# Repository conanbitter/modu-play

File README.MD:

# ModuPlay

*The console that's only as smart as the cartridge you plug in.*

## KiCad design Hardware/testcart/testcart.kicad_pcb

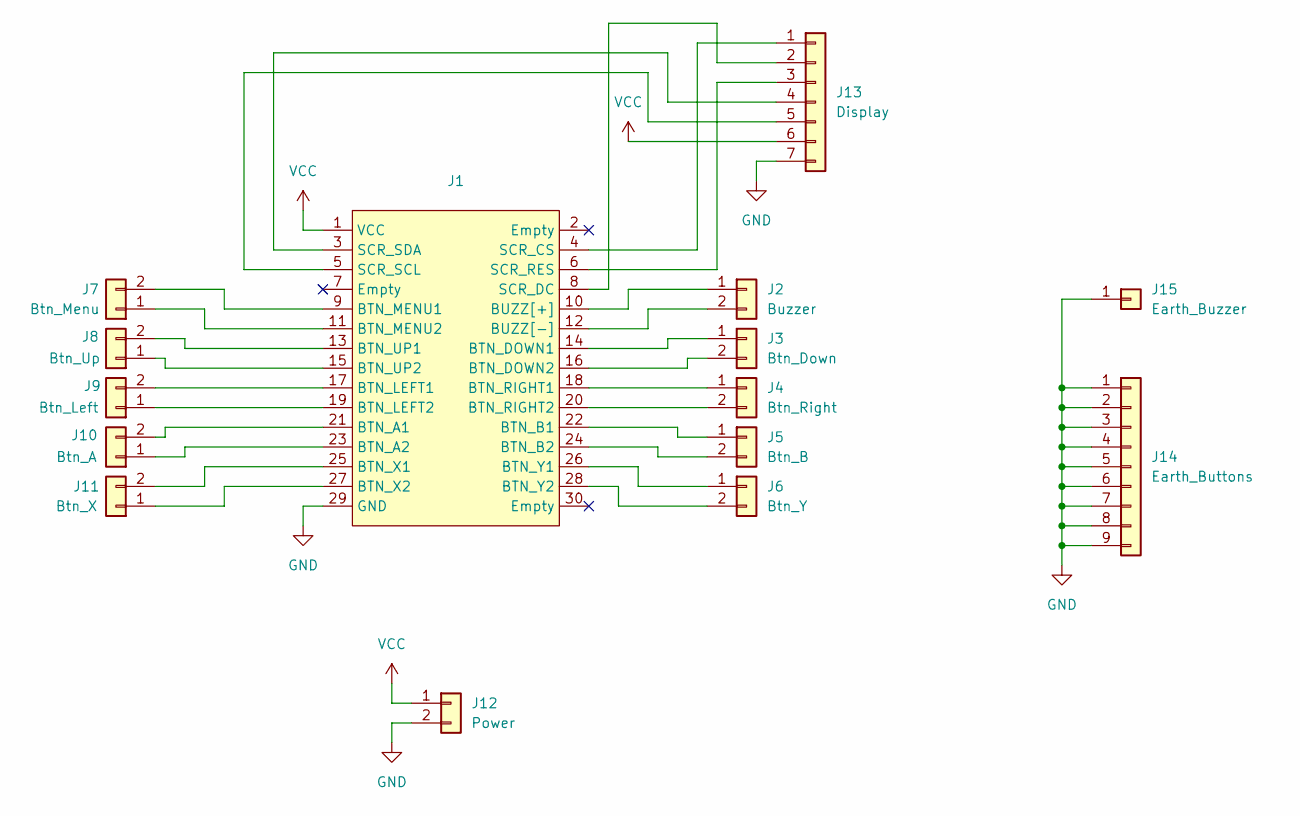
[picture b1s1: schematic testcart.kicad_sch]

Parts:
J1: Edge_Connector
J2: Buzzer; PinHeader_1x02_P2.54mm_Vertical
J3: Btn_Down; PinHeader_1x02_P2.54mm_Vertical
J4: Btn_Right; PinHeader_1x02_P2.54mm_Vertical
J5: Btn_B; PinHeader_1x02_P2.54mm_Vertical
J6: Btn_Y; PinHeader_1x02_P2.54mm_Vertical
J7: Btn_Menu; PinHeader_1x02_P2.54mm_Vertical
J8: Btn_Up; PinHeader_1x02_P2.54mm_Vertical
J9: Btn_Left; PinHeader_1x02_P2.54mm_Vertical
J10: Btn_A; PinHeader_1x02_P2.54mm_Vertical
J11: Btn_X; PinHeader_1x02_P2.54mm_Vertical
J12: Power; PinHeader_1x02_P2.54mm_Vertical
J13: Display; PinHeader_1x07_P2.54mm_Vertical
J14: Earth_Buttons; PinHeader_1x09_P2.54mm_Vertical
J15: Earth_Buzzer; PinHeader_1x01_P2.54mm_Vertical

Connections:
GND: J1.29 (GND), J12.2, J13.7, J14.1, J14.2, J14.3, J14.4, J14.5, J14.6, J14.7, J14.8, J14.9, J15.1
unnamed: J1.21 (BTN_A1), J10.2
unnamed: J1.23 (BTN_A2), J10.1
unnamed: J1.22 (BTN_B1), J5.1
unnamed: J1.24 (BTN_B2), J5.2
unnamed: J1.14 (BTN_DOWN1), J3.1
unnamed: J1.16 (BTN_DOWN2), J3.2
unnamed: J1.17 (BTN_LEFT1), J9.2
unnamed: J1.19 (BTN_LEFT2), J9.1
unnamed: J1.9 (BTN_MENU1), J7.2
unnamed: J1.11 (BTN_MENU2), J7.1
unnamed: J1.18 (BTN_RIGHT1), J4.1
unnamed: J1.20 (BTN_RIGHT2), J4.2
unnamed: J1.13 (BTN_UP1), J8.2
unnamed: J1.15 (BTN_UP2), J8.1
unnamed: J1.25 (BTN_X1), J11.2
unnamed: J1.27 (BTN_X2), J11.1
unnamed: J1.26 (BTN_Y1), J6.1
unnamed: J1.28 (BTN_Y2), J6.2
unnamed: J1.10 (BUZZ[+]), J2.1
unnamed: J1.12 (BUZZ[-]), J2.2
unnamed: J1.4 (SCR_CS), J13.1
unnamed: J1.8 (SCR_DC), J13.2
unnamed: J1.6 (SCR_RES), J13.3
unnamed: J1.5 (SCR_SCL), J13.5
unnamed: J1.3 (SCR_SDA), J13.4
VCC: J1.1 (VCC), J12.1, J13.6

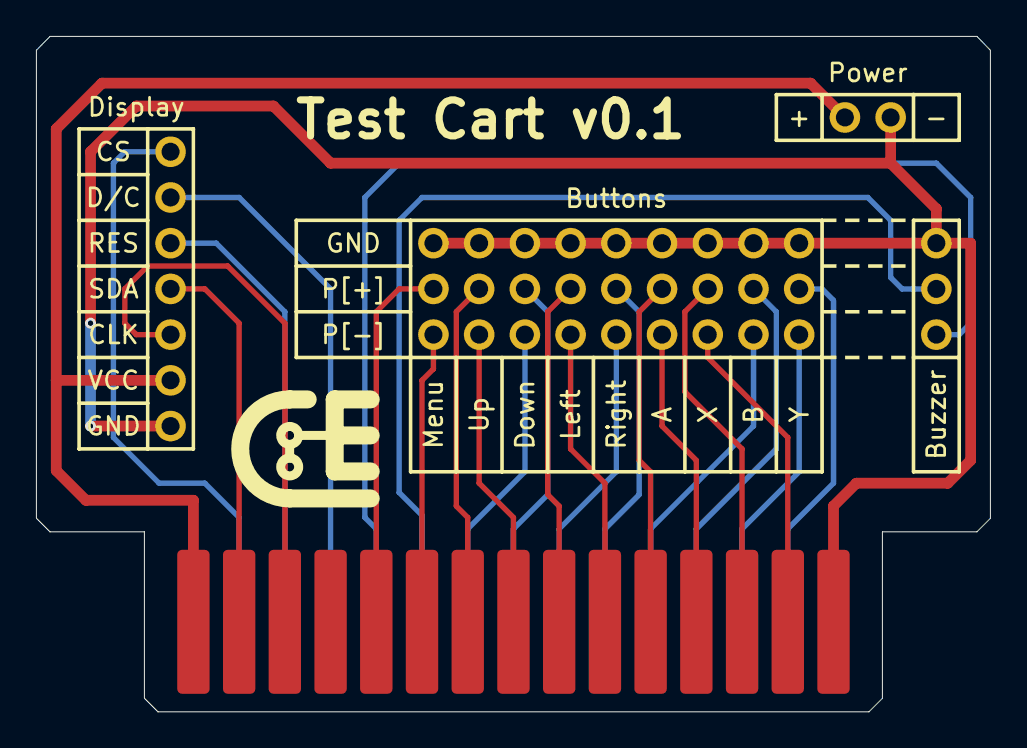
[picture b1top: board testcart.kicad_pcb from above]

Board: 2 copper layers, 53.0 x 37.5 mm, 15 parts (0 on the bottom side), 27 nets.

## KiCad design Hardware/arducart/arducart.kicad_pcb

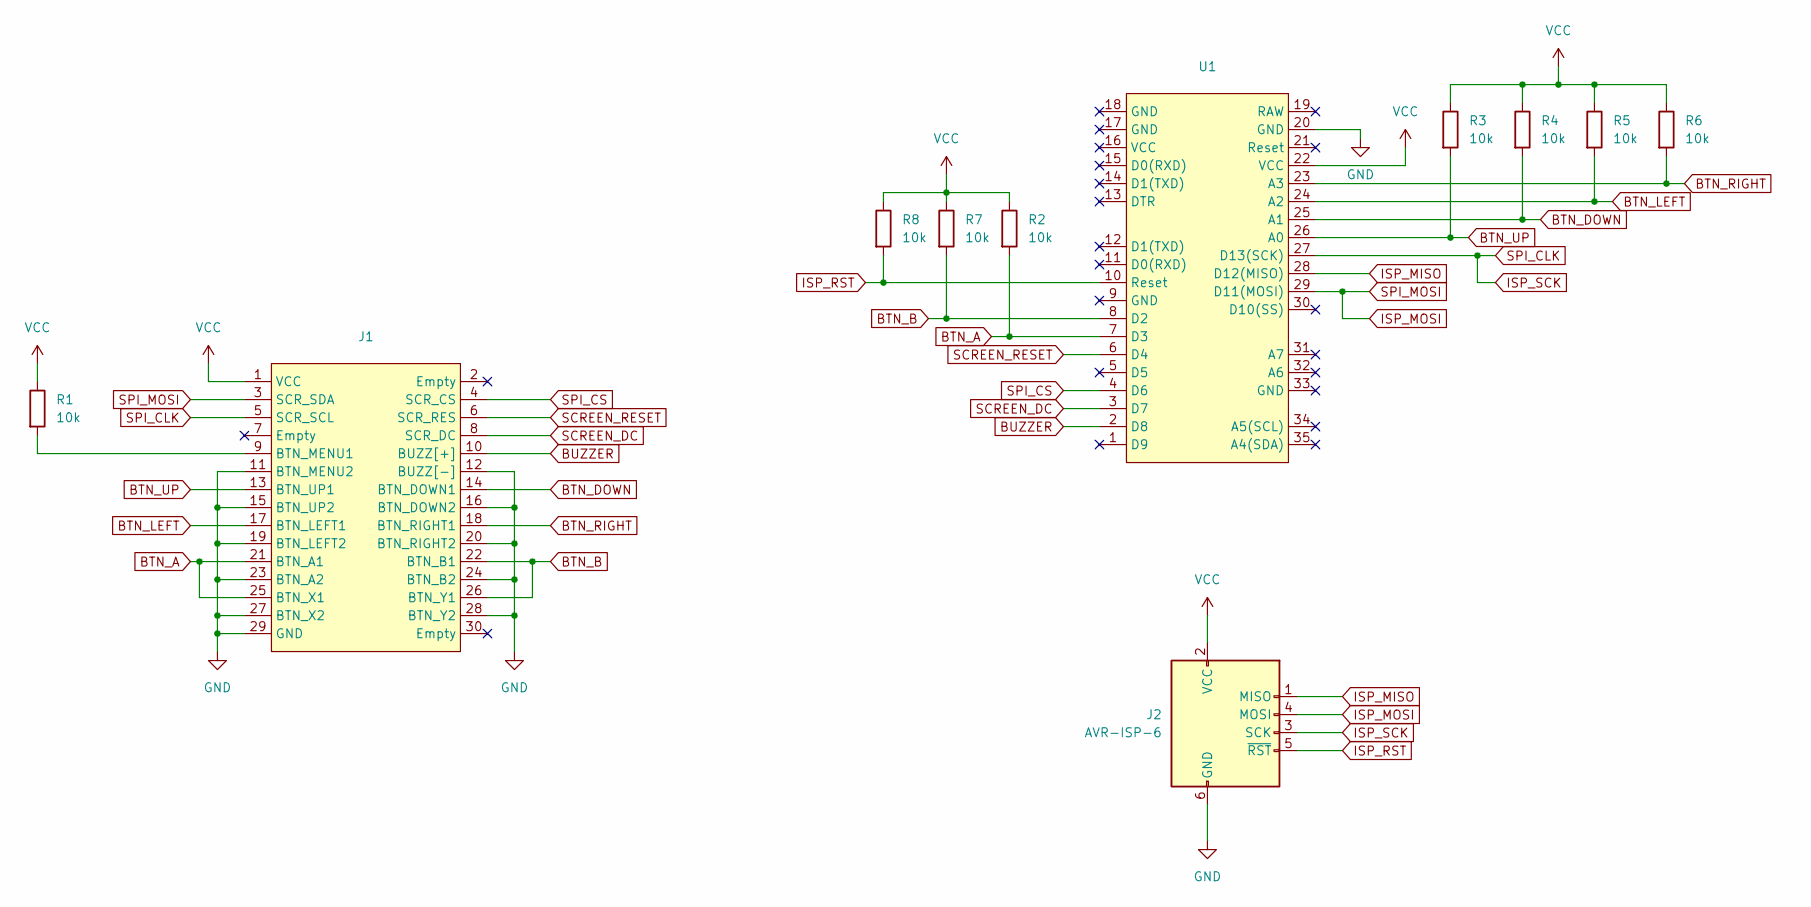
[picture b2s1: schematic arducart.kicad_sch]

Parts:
J1: Edge_Connector
J2: AVR-ISP-6; PinHeader_2x03_P2.54mm_Horizontal
R1, R2, R3, R4, R5, R6, R7, R8: 10k; R_1206_3216Metric_Pad1.30x1.75mm_HandSolder
U1: Arduino_Pro_Mini

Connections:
BTN_A: J1.21 (BTN_A1), J1.25 (BTN_X1), R2.2, U1.7 (D3)
BTN_B: J1.22 (BTN_B1), J1.26 (BTN_Y1), R7.2, U1.8 (D2)
BTN_DOWN: J1.14 (BTN_DOWN1), R4.2, U1.25 (A1)
BTN_LEFT: J1.17 (BTN_LEFT1), R5.2, U1.24 (A2)
BTN_RIGHT: J1.18 (BTN_RIGHT1), R6.2, U1.23 (A3)
BTN_UP: J1.13 (BTN_UP1), R3.2, U1.26 (A0)
BUZZER: J1.10 (BUZZ[+]), U1.2 (D8)
GND: J1.11 (BTN_MENU2), J1.12 (BUZZ[-]), J1.15 (BTN_UP2), J1.16 (BTN_DOWN2), J1.19 (BTN_LEFT2), J1.20 (BTN_RIGHT2), J1.23 (BTN_A2), J1.24 (BTN_B2), J1.27 (BTN_X2), J1.28 (BTN_Y2), J1.29 (GND), J2.6 (GND), U1.20 (GND)
ISP_MISO: J2.1 (MISO), U1.28 (D12(MISO))
ISP_MOSI: J1.3 (SCR_SDA), J2.4 (MOSI), U1.29 (D11(MOSI))
ISP_RST: J2.5 (~RST), R8.2, U1.10 (Reset)
ISP_SCK: J1.5 (SCR_SCL), J2.3 (SCK), U1.27 (D13(SCK))
unnamed: J1.9 (BTN_MENU1), R1.2
SCREEN_DC: J1.8 (SCR_DC), U1.3 (D7)
SCREEN_RESET: J1.6 (SCR_RES), U1.6 (D4)
SPI_CS: J1.4 (SCR_CS), U1.4 (D6)
VCC: J1.1 (VCC), J2.2 (VCC), R1.1, R2.1, R3.1, R4.1, R5.1, R6.1, R7.1, R8.1, U1.22 (VCC)

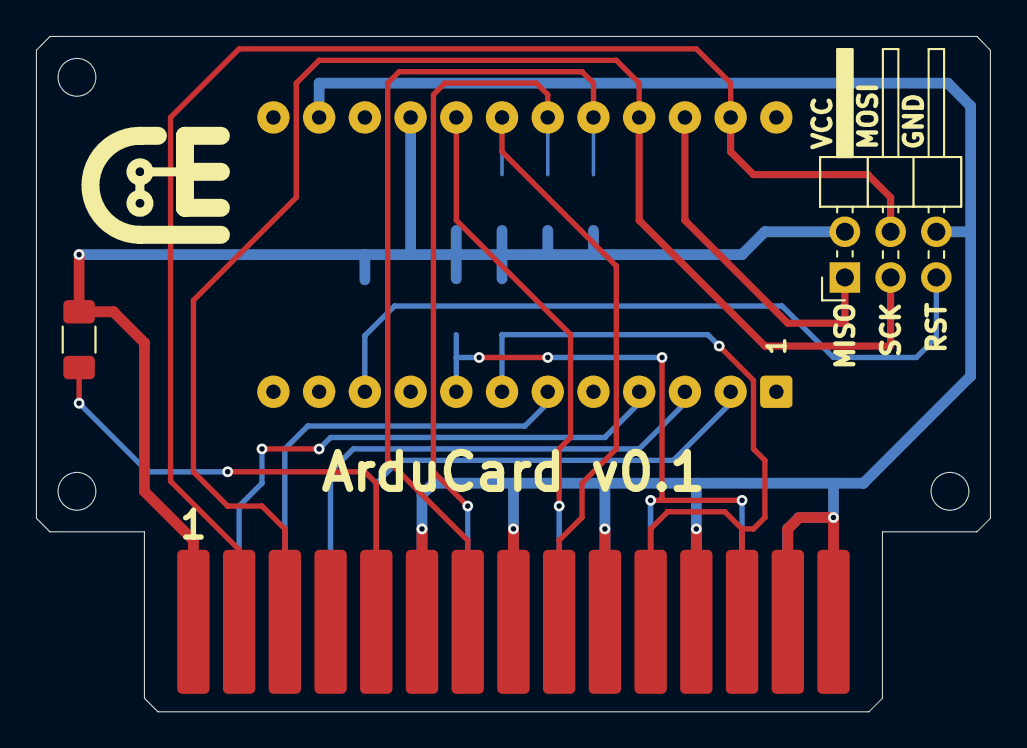
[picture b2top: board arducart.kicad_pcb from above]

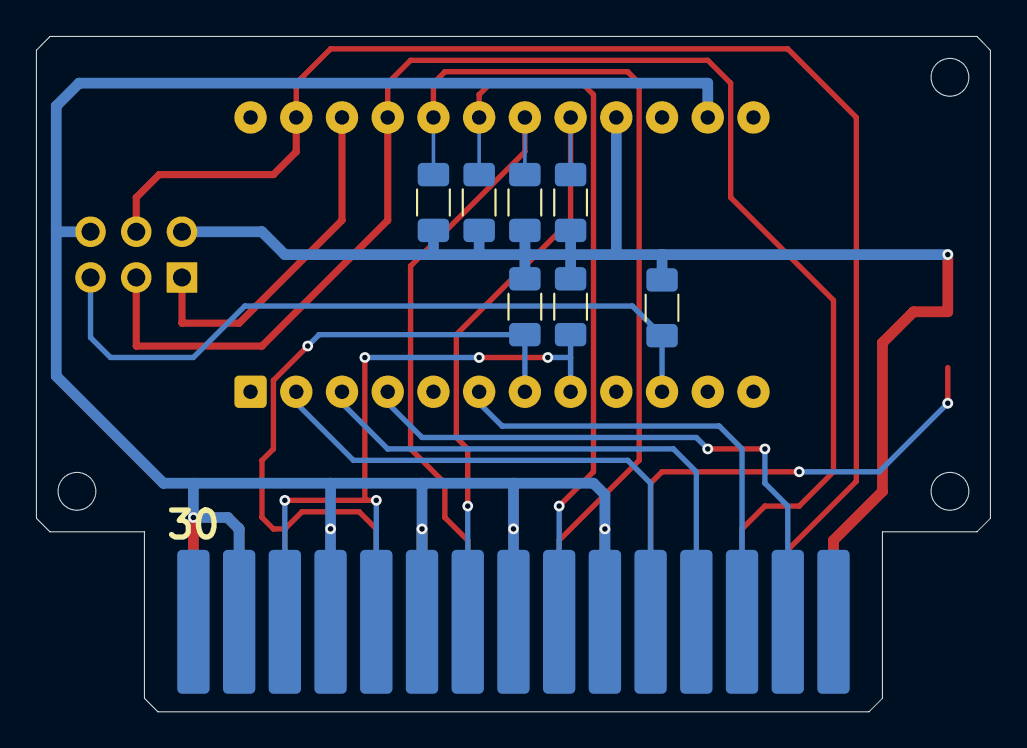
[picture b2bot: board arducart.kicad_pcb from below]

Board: 2 copper layers, 53.0 x 37.5 mm, 11 parts (7 on the bottom side), 17 nets.

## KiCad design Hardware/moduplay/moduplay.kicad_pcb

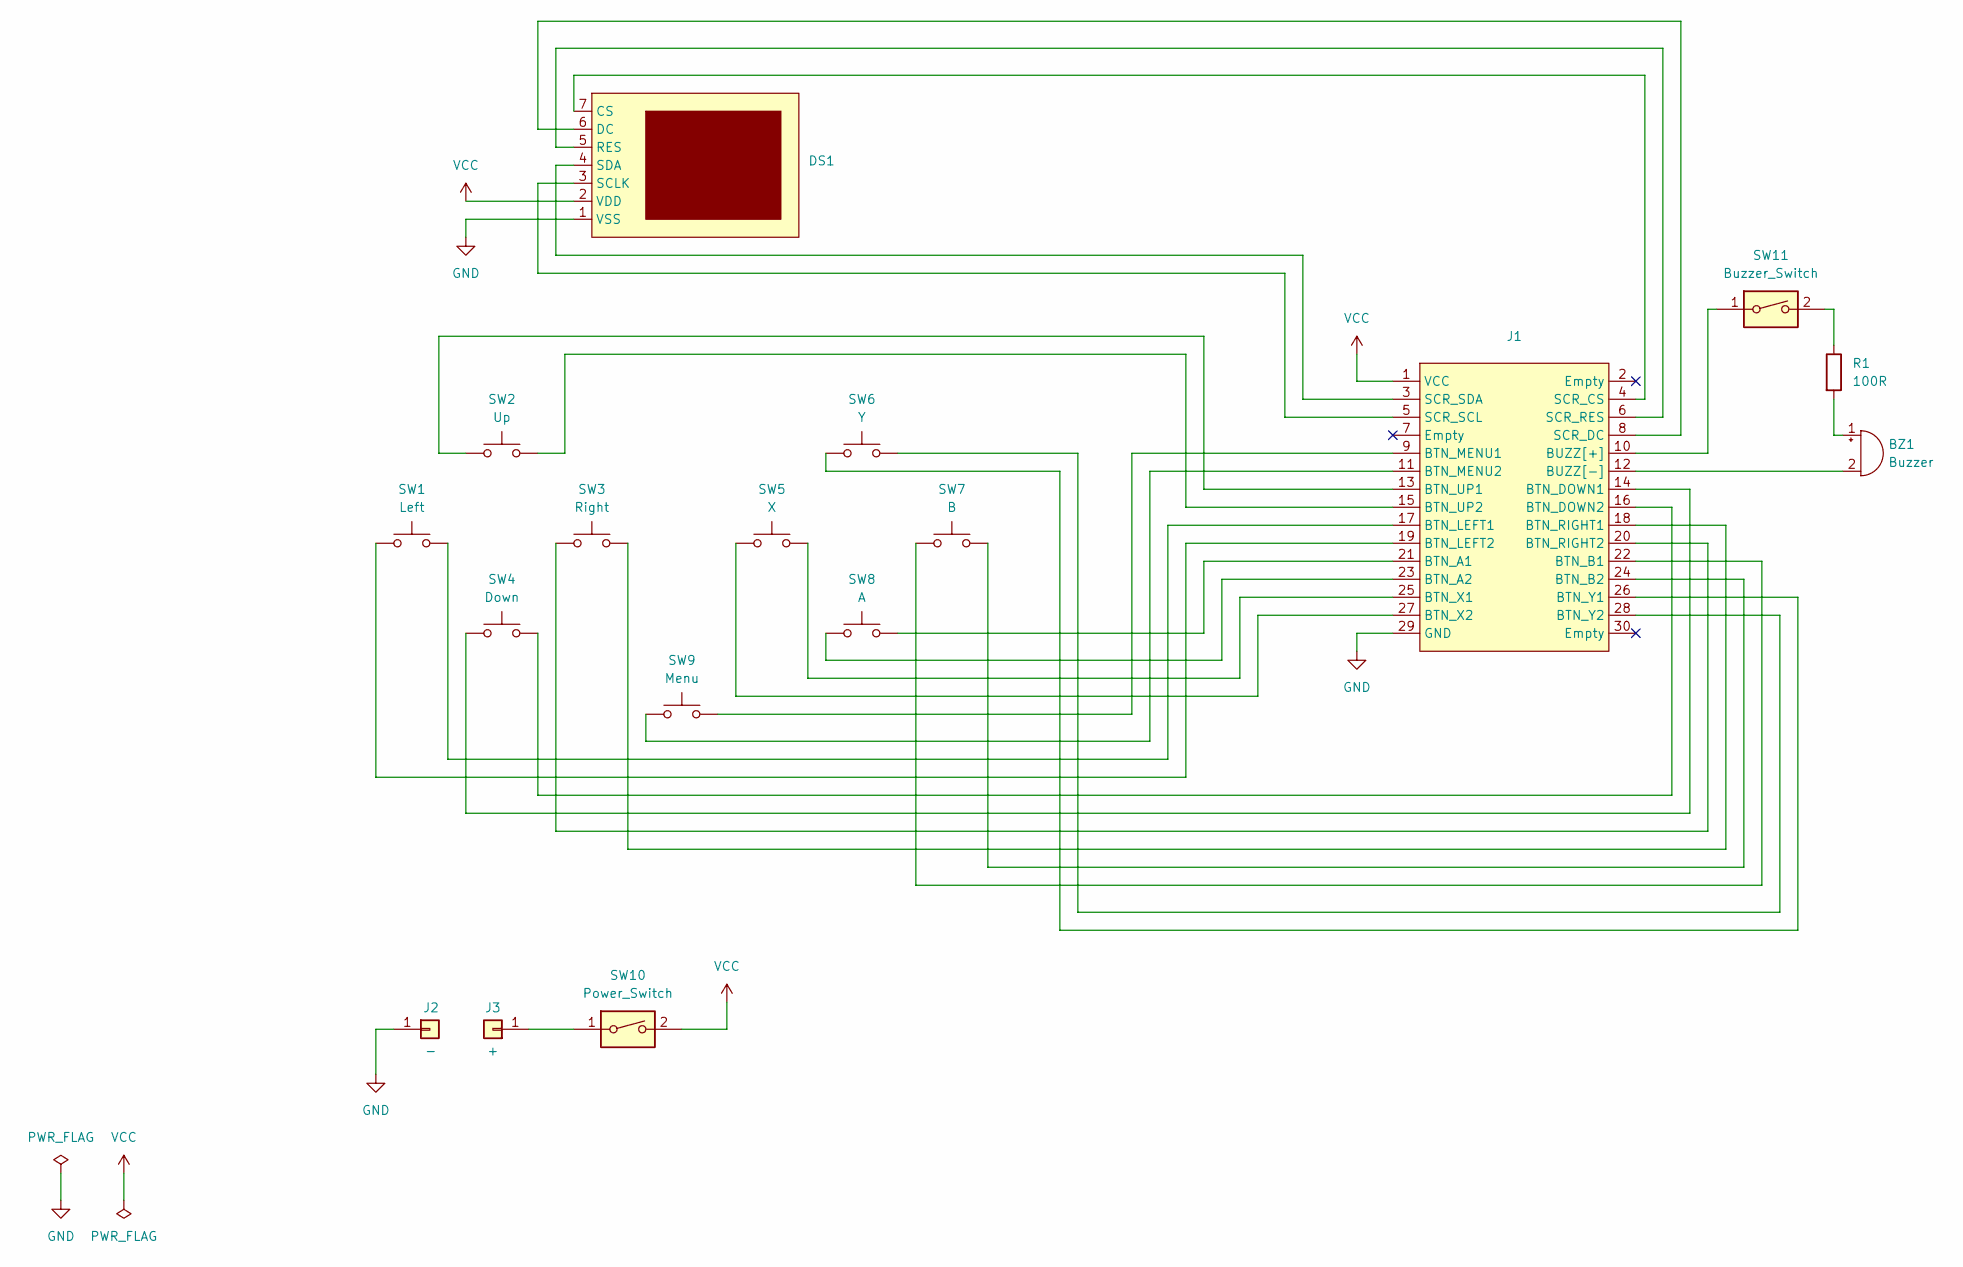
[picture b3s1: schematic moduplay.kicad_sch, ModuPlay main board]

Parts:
BZ1: Buzzer; Buzzer_TDK_PS1240P02BT_D12.2mm_H6.5mm
DS1: Screen_Full
J1: Edge_Connector_Slot
J2: -; Power_Port_Single_Minus
J3: +; Power_Port_Single_Plus
R1: 100R; R_1206_3216Metric_Pad1.30x1.75mm_HandSolder
SW1: Left; SW_PUSH_6mm_H5mm
SW2: Up; SW_PUSH_6mm_H5mm
SW3: Right; SW_PUSH_6mm_H5mm
SW4: Down; SW_PUSH_6mm_H5mm
SW5: X; SW_PUSH_6mm_H5mm
SW6: Y; SW_PUSH_6mm_H5mm
SW7: B; SW_PUSH_6mm_H5mm
SW8: A; SW_PUSH_6mm_H5mm
SW9: Menu; SW_PUSH_6mm_H5mm
SW10: Power_Switch
SW11: Buzzer_Switch; Power_Switch

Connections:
GND: DS1.1 (VSS), J1.29 (GND), J2.1
unnamed: BZ1.1 (+), R1.2
unnamed: BZ1.2 (-), J1.12 (BUZZ[-])
unnamed: DS1.7 (CS), J1.4 (SCR_CS)
unnamed: DS1.6 (DC), J1.8 (SCR_DC)
unnamed: DS1.5 (RES), J1.6 (SCR_RES)
unnamed: DS1.3 (SCLK), J1.5 (SCR_SCL)
unnamed: DS1.4 (SDA), J1.3 (SCR_SDA)
unnamed: J1.21 (BTN_A1), SW8.2
unnamed: J1.23 (BTN_A2), SW8.1
unnamed: J1.22 (BTN_B1), SW7.1
unnamed: J1.24 (BTN_B2), SW7.2
unnamed: J1.14 (BTN_DOWN1), SW4.1
unnamed: J1.16 (BTN_DOWN2), SW4.2
unnamed: J1.17 (BTN_LEFT1), SW1.2
unnamed: J1.19 (BTN_LEFT2), SW1.1
unnamed: J1.9 (BTN_MENU1), SW9.2
unnamed: J1.11 (BTN_MENU2), SW9.1
unnamed: J1.18 (BTN_RIGHT1), SW3.2
unnamed: J1.20 (BTN_RIGHT2), SW3.1
unnamed: J1.13 (BTN_UP1), SW2.1
unnamed: J1.15 (BTN_UP2), SW2.2
unnamed: J1.25 (BTN_X1), SW5.2
unnamed: J1.27 (BTN_X2), SW5.1
unnamed: J1.26 (BTN_Y1), SW6.1
unnamed: J1.28 (BTN_Y2), SW6.2
unnamed: J1.10 (BUZZ[+]), SW11.1
unnamed: J3.1, SW10.1
unnamed: R1.1, SW11.2
VCC: DS1.2 (VDD), J1.1 (VCC), SW10.2

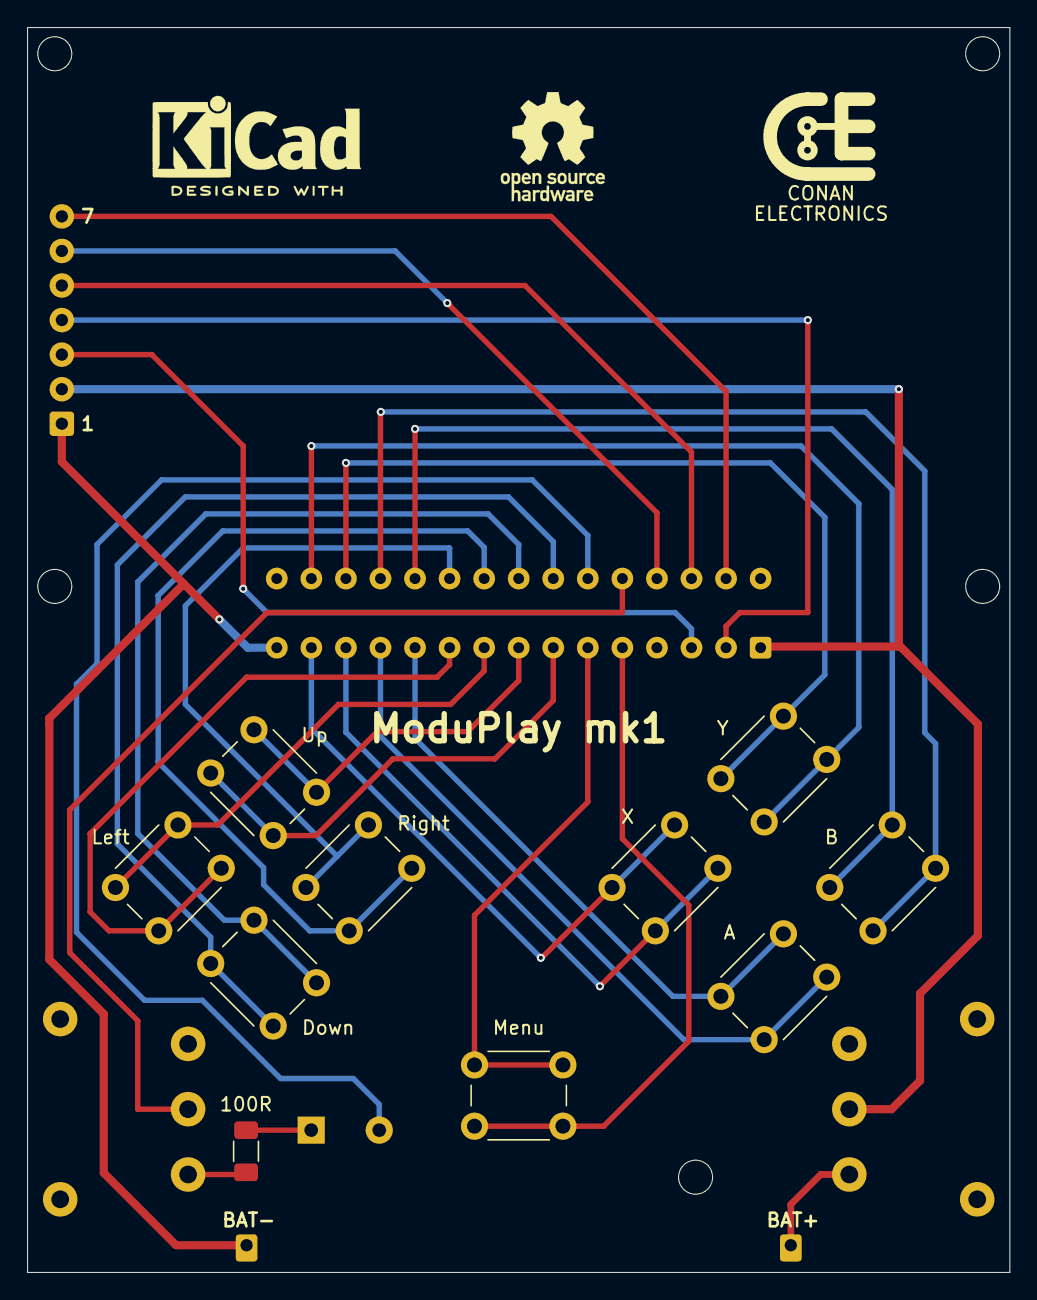
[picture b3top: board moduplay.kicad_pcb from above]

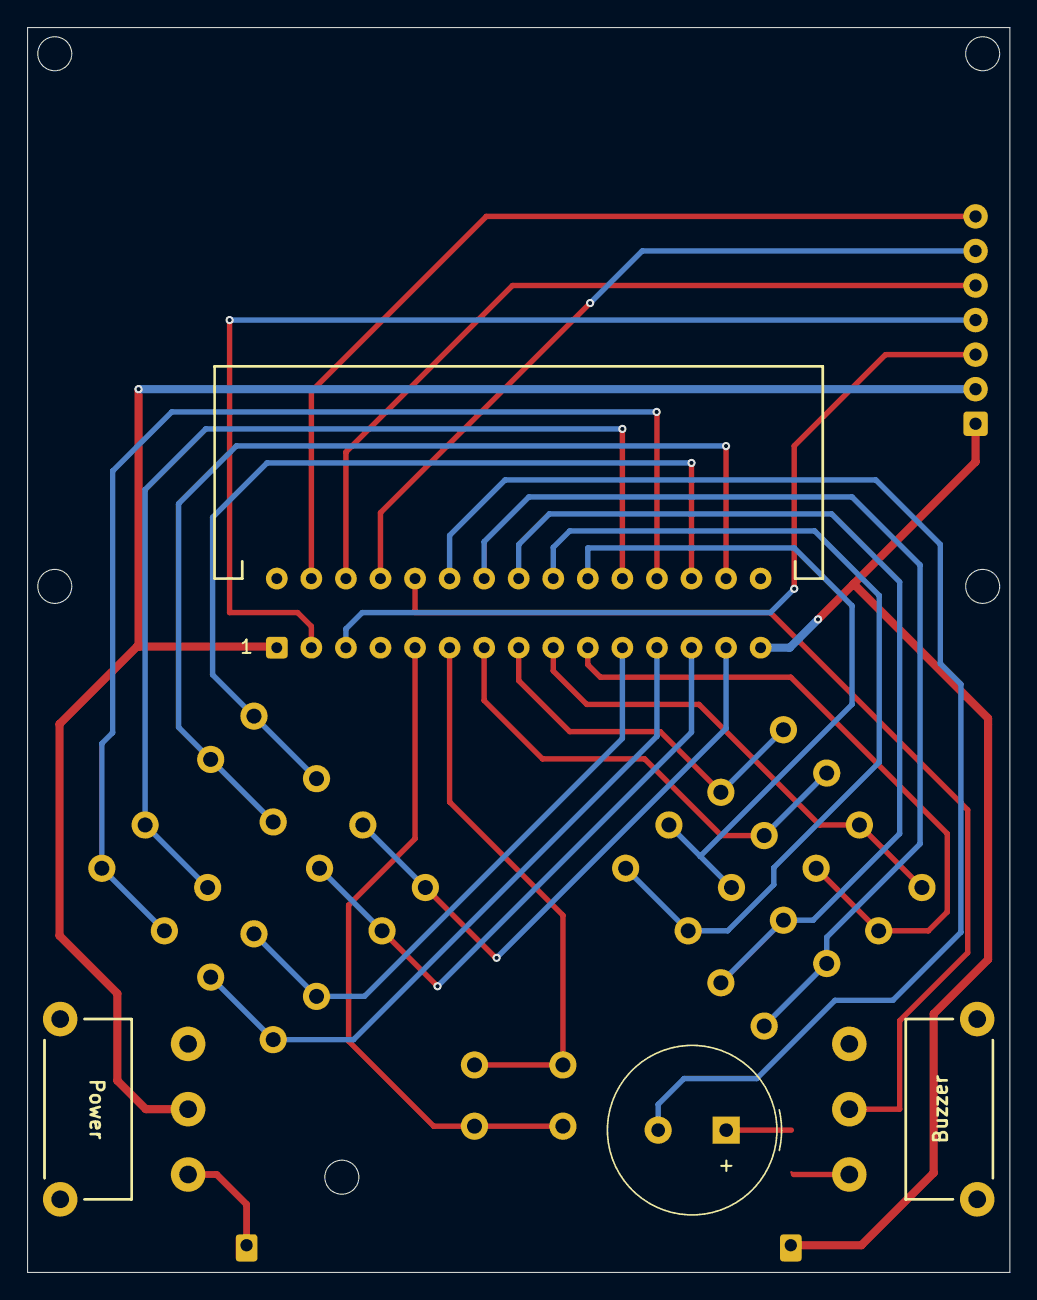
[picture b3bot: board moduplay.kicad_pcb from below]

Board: 2 copper layers, 72.2 x 91.5 mm, 17 parts (4 on the bottom side), 30 nets.

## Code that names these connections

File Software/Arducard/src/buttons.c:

#include "buttons.h"
#include <avr/io.h>
#include "arduino.h"

#define BTN_UP A0
#define BTN_DOWN A1
#define BTN_LEFT A2
#define BTN_RIGHT A3
#define BTN_A D3
#define BTN_B D2

void btn_init()
{
    CINPUT(BTN_UP);
    CINPUT(BTN_DOWN);
    CINPUT(BTN_LEFT);
    CINPUT(BTN_RIGHT);
    CINPUT(BTN_A);
    CINPUT(BTN_B);
}

int btn_get(int button)
{
    switch (button)
    {
    case 0:return !CREAD(BTN_UP);
    case 1:return !CREAD(BTN_DOWN);
    case 2:return !CREAD(BTN_LEFT);
    case 3:return !CREAD(BTN_RIGHT);
    case 4:return !CREAD(BTN_A);
    case 5:return !CREAD(BTN_B);
    }

}

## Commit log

2025-05-25 Add readme
2025-05-25 Add hardware project
2025-05-25 Add basic components
2025-05-25 Finish scheme
2025-05-26 Add footprints
2025-05-26 Improve connector, add buzzer wire
2025-05-26 Add buzzer
2025-05-26 Add ports
2025-05-26 Drawt of PCB
2025-05-27 Add buzzer switch, separete baterry connectors, further PCD development
2025-05-27 Next iteration designing PCB
2025-05-28 Try to include whole screen
2025-05-29 Improve screen position
2025-06-01 First draft of routing
2025-06-02 Next iteration on PCB
2025-06-02 Final draft of PCB design
2025-06-02 Adjust export settings
2025-06-09 Begin working on ArduCart
2025-06-10 Add PiPico2 and ESP32C3
2025-06-10 Add polarity to buzzer
2025-06-10 First draft of ArduCart schematic
2025-06-11 First draft of PCB design
2025-06-11 First routing
2025-06-11 Finish PCB design
2025-06-11 Add logo on PCBs
2025-06-11 Add TestCart
2025-06-11 First design draft
2025-06-12 Finish design of Test Cart
2025-06-21 Add holes to PCB
2025-06-21 Add holes, add space for cartrige case
2025-06-21 Fixes to comply to design rules
2025-06-21 Fix buzzer connection
2025-09-16 Tune export settings
2025-09-16 Setup Arducard firmware
2025-09-18 Attempts to make a screen driver
2025-09-18 Fix data/command switch
2025-09-18 Fix hardware SPI
2025-09-18 Clean up screen driver code
2025-09-19 Finish developing screen API
2025-09-19 Implement basic screen driver functions
2025-09-19 Testing buttons
2025-09-20 Fix buttons
2025-09-20 Fix inline functions
2025-09-20 Setup timer
2025-09-20 Implement and test screen buffer
2025-09-22 Begin working on simulator
2025-09-22 Add screen texture
2025-09-22 Add screen buffer
2025-09-23 Rearrange code
2025-09-23 Implement input system
2025-09-24 Implement image converter, add assets
2025-09-24 Fixes in output file format
2025-09-25 Implement basic drawing without border check
